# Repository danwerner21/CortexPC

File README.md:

# CortexPC

This is an ATX format implimentation of the Mini-Cortex system by Paul Ruizendaal and Stuart Conner.  The Mini-Cortex system is a further development of a TMS 9995 breadboard project to produce a system similar to a Powertran Cortex, but using more modern components. The system is based around a TMS 9995 running at 3 MHz, with 32K byte EEPROM, and will use 512K bytes of RAM  accessed through a memory mapper. An on-board serial port and IDE interface exists on the card.  There is also provisions for a TMS9918 clone, a keyboard and some expansion slots -- these are not totally supported by the firmware at this time however.

The main EEPROM image provides a boot menu which enables the user to select between the EVMBUG system monitor from TI's TMS 9995 Evaluation Module, a port of the Powertran Cortex Power BASIC made for a TM 990 computer, the Marinchip Disk Executive (MDEX) operating system, and an implementation of V6 Unix including a C compiler.

[Much more information can be found at Stuart's site](https://www.stuartconner.me.uk/mini_cortex/mini_cortex.htm)

[Source code for the Cortex Version of Unix V6 and a ton more TI990 software (including cross development tools) can be found here on Dave Pitts' TI-990 web page.](https://www.cozx.com/dpitts/ti990.html)

## Memory Map
The memory map is shown in the table below.

```
Memory Address	Mapped To
>0000 - >7FFF	ROM when enabled, otherwise RAM
>8000 - >EFFF	RAM
>F000 - >F0FB	TMS 9995 internal RAM
>F0FC - >FDFF	RAM
>FE00 - >FE03	CF card ATA registers 
>FE08 - >FE08	SN76489 SOUND
>FE20 - >FE21	Video
>FE40 - >FE4F	Memory mapper registers 0-15 
>FE60 - >FE7F	SID Chip
>FE80 - >FEBF	Offboard IO (ports $80-$FF)
>FFF0 - >FFF9	RAM
>FFFA - >FFFF	TMS 9995 internal RAM

CRU Address	Mapped To
>0000 - >003F	TMS 9902 registers
>0040 - >007F	Control signal latch (further details here)
 	(Plus processor internal CRU bits)
    
(Note that in TI Speak ">" means Hexidecimal, so for the rest of us >FFFA is the same as $FFFA or 0xFFFA or FFFAH)
```
[for more information see Stuart's site](https://www.stuartconner.me.uk/mini_cortex/mini_cortex.htm)

## Creating CF card Image for MDEX and Unix

The CF card has to be newly formatted with an MBR (master boot record), a single partition formatted as FAT32, and a cluster size of 4096 bytes - the CF card needs to be at least 256 MB to support this. Not all brands/sizes of CF card seem to work - you may have more success with an older, low capacity card. A SanDisk 2.0GB card with a "SDCFB" marking on the back works well.

It can be problematic formatting a new card using Windows 10 as it does not always seem to write an MBR to the card. I use a formatting utility called Rufus [details and download here](https://rufus.ie/en/) with Boot selection==Non bootable, Partition Scheme==MBR, File System=FAT32, and Cluster Size= 4096 Bytes. Once the card is correctly formatted, use Windows to write the four files from the software folder ZIP filedirectly to the card.
[for more information see Stuart's site](https://www.stuartconner.me.uk/mini_cortex/mini_cortex.htm)

## Jumper Settings
```
  P6 - ATX Case Power Button
  JP1- ATX Case Reset Button
  JP3- SID Chip CS (Some SID replacement chips need 2-3, default 1-2)
  J21- Enable SID Audio Amp
  J20- SID Speaker Out
  J22- SN76489 Audio Amp
  J23- SN76489 Speaker Out
  J1 - F18A TANG NANO Connector 
  J4 - Serial Interrupt Enabled (Required for UNIX)
  J5 - TTL Serial Interface
  J6 - TTL Serial Power Enable
  JP2- Enable Keyboard Interface
  JP4- ATX Case IDE Led output
  JP5- IDE Power Enable (2-3 for VCC on IDE Pin 20)
  
```
## Powering up
The serial port on the TMS9995 board is configured for 9600 Baud, 7 data bits, even parity, one stop bit, no flow control.

The EVMBUG monitor and the boot loaders for MDEX and Unix, are stored on a single 32K byte EEPROM. The required application is selected from a boot menu. To display the boot menu, connect the board to a configured serial port on a PC, apply power then press any key.

You should then see:
```
  ___         _           ___  ___
 / __|___ _ _| |_ _____ _| _ \/ __|
| (__/ _ \ '_|  _/ -_) \ /  _/ (__
 \___\___/_|  \__\___/_\_\_|  \___|

TMS9995 COMPUTER SYSTEM
BIOS V1.0

PRESS 1 FOR EVMBUG MONITOR
PRESS 2 FOR MDEX
PRESS 3 FOR UNIX
```
To select a software application from the menu, press the corresponding numeric key.

## Useful Links
MDEX documentation is available on the site http://www.powertrancortex.com/documentation.html. The documentation and MDEX disks were recovered and made available by Dave Hunter, the owner of the www.powertrancortex.com site. Porting of the MDEX files to the Mini-Cortex was by Paul Ruizendaal. On the Mini-Cortex, the files are stored in two emulated disks on the CF card.

The first version of Unix ported was LSX Unix (https://www.mailcom.com/lsx/), which was designed to run with 40K byte RAM and two 256K byte floppies. LSX Unix was adapted from Unix V6 by Dr. Heinz Lycklama (https://www.60bits.net/msu/mycomp/terak/termubel.htm). This port has been further ported to the TI 990 minicomputer by Dave Pitts, who has also made improvements to the code build system.

[Dave Pitts' TI-990 web page.](https://www.cozx.com/dpitts/ti990.html)
[EVMBUG documentation](https://www.stuartconner.me.uk/tibug_evmbug/tibug_evmbug.htm#evmbug)

## Bugs/To Do
* No known bugs in V0.9
* Keyboard Firmware needs created and tested

## Troubleshooting

The first test image tests just the processor (TMS9995_test_1_eprom_image), the EPROM and the EPROM chip select logic. Program and fit the EPROM, power on, press the reset switch.  The CPU should execute a loop from ROM., then use the logic probe to check for a series of pulses on pin 20 of the EPROM every 2 seconds or so. 

If the first test passes, repeat with the second test image (TMS9995_test_2_eprom_image), which also tests the RAM and the RAM chip select logic. With the second test, a series of pulses should be seen on pin 20 of the EPROM every 6 seconds or so.

The third test image has two versions.   The first version configures the serial port to 9600 Baud, 7 bits/character, even parity, 2 stops bits, no flow control, and then loops continually sending the ASCII characters >21 ("!") to >7E .  This version tests most of the system including ROM and RAM.   The second version is a ROM only version. It also configures the serial port to 9600 Baud, 7 bits/character, even parity, 2 stops bits, no flow control, and then loops continually sending the ASCII characters >21 ("!") to >7E , but does not use any external RAM.

## Patches
* none needed for V0.9
 
## BOM
Reference|Value|Qty|Description
---------|-----|---|-----------
C1,C2,C3,C4,C5,C6,C7,C8,C9,C10,C11,C12,C13,C14,C15,C16,C17,C19,C21,C23,C25,C27,C29|0.1u|23|
C18,C20,C22,C24|10u|4|
C26|22u|1|
C28|47uF|1|
C30|1uF|1|Polarized capacitor
C31|10uF|1|Polarized capacitor
C32|0.1 uF|1|Unpolarized capacitor
C33|0.01 uF|1|Unpolarized capacitor
C34|100µF|1|
C35|0.1µF|1|
C40,C41|15pf|2|
D1|PWR|1|LED
D2|IDLE|1|LED
D3|MAP|1|LED
D5|1N5817|1|20V 1A Schottky Barrier Rectifier Diode, DO-41
D6|IDE ACT|1|LED
D8|Tx|1|LED
D9|Rx|1|LED
D10,D11|1N4148|2|100V 0.15A standard switching diode, DO-35
J1|F18A TANG NANO Connector|1|Generic connector, double row, 02x10, odd/even pin numbering scheme (row 1 odd numbers, row 2 even numbers), script generated (kicad-library-utils/schlib/autogen/connector/)
J2,J8,J11,J13,J15,J17|IRQ Selection|6|Generic connector, double row, 02x06, odd/even pin numbering scheme (row 1 odd numbers, row 2 even numbers), script generated (kicad-library-utils/schlib/autogen/connector/)
J3,J10,J12,J14,J16,J18|Bus_I_not_SA_8bit|6|8-bit ISA-PC bus connector
J4|Enable Serial Int|1|Generic connector, single row, 01x02, script generated
J5|TTL SERIAL 0|1|
J6|TTL SER 0 PWR|1|
J7|USER OUT|1|Generic connector, single row, 01x07, script generated
J9|AUDIO OUT|1|coaxial connector (BNC, SMA, SMB, SMC, Cinch/RCA, LEMO, ...)
J19|Parallel Keyboard IN|1|Generic connector, single row, 01x11, script generated
JP1|JUMPER|1|Generic connector, single row, 01x02, script generated (kicad-library-utils/schlib/autogen/connector/)
JP4|EXT IDE LED|1|
JP5|IDE PWR|1|
P1|14.31818 MHz CLK|1|
P4|8 BIT IDE (CF)|1|
P5|CONN_10X2|1|Generic connector, double row, 02x10, odd/even pin numbering scheme (row 1 odd numbers, row 2 even numbers), script generated (kicad-library-utils/schlib/autogen/connector/)
P6|POWER_SW|1|Generic connector, single row, 01x02, script generated (kicad-library-utils/schlib/autogen/connector/)
R1,R3,R6,R7,R11,R12,R13,R17|470|8|-- mixed values --
R2,R4,R8,R10,R14|10K|5|
R5|1000|1|Resistor
R9|10Ω|1|
R16,R18|10k|2|Resistor
SW1|RESET|1|Push button switch, generic, two pins
SW2|POWER|1|Push button switch, generic, two pins
U1|74LS14|1|
U2|74LS07|1|
U3|TMS9995-DIP_1|1|
U4|74LS04|1|
U5,U27|74LS74|2|-- mixed values --
U6|74LS112|1|
U7|SN76489|1|
U8|DS1233|1|
U9|SRAM_512K|1|512K x 8 Low Power CMOS RAM, DIP-32
U10|TMS9918 EMU|1|
U11,U30|GAL22V10|2|
U12,U13|74LS32|2|Quad 2-input OR
U14,U28,U29,U31|74LS244|4|Octal Buffer and Line Driver With 3-State Output, active-low enables, non-inverting outputs
U15|74LS138|1|
U17|74LS688|1|
U18|27C256|1|
U21|TMS9902A|1|
U22|74LS259|1|
U23|74LS612-DIP|1|
U25|74LS245|1|Octal BUS Transceivers, 3-State outputs
U26|74HCT14|1|Hex inverter schmitt trigger
Y1|12MHz|1|

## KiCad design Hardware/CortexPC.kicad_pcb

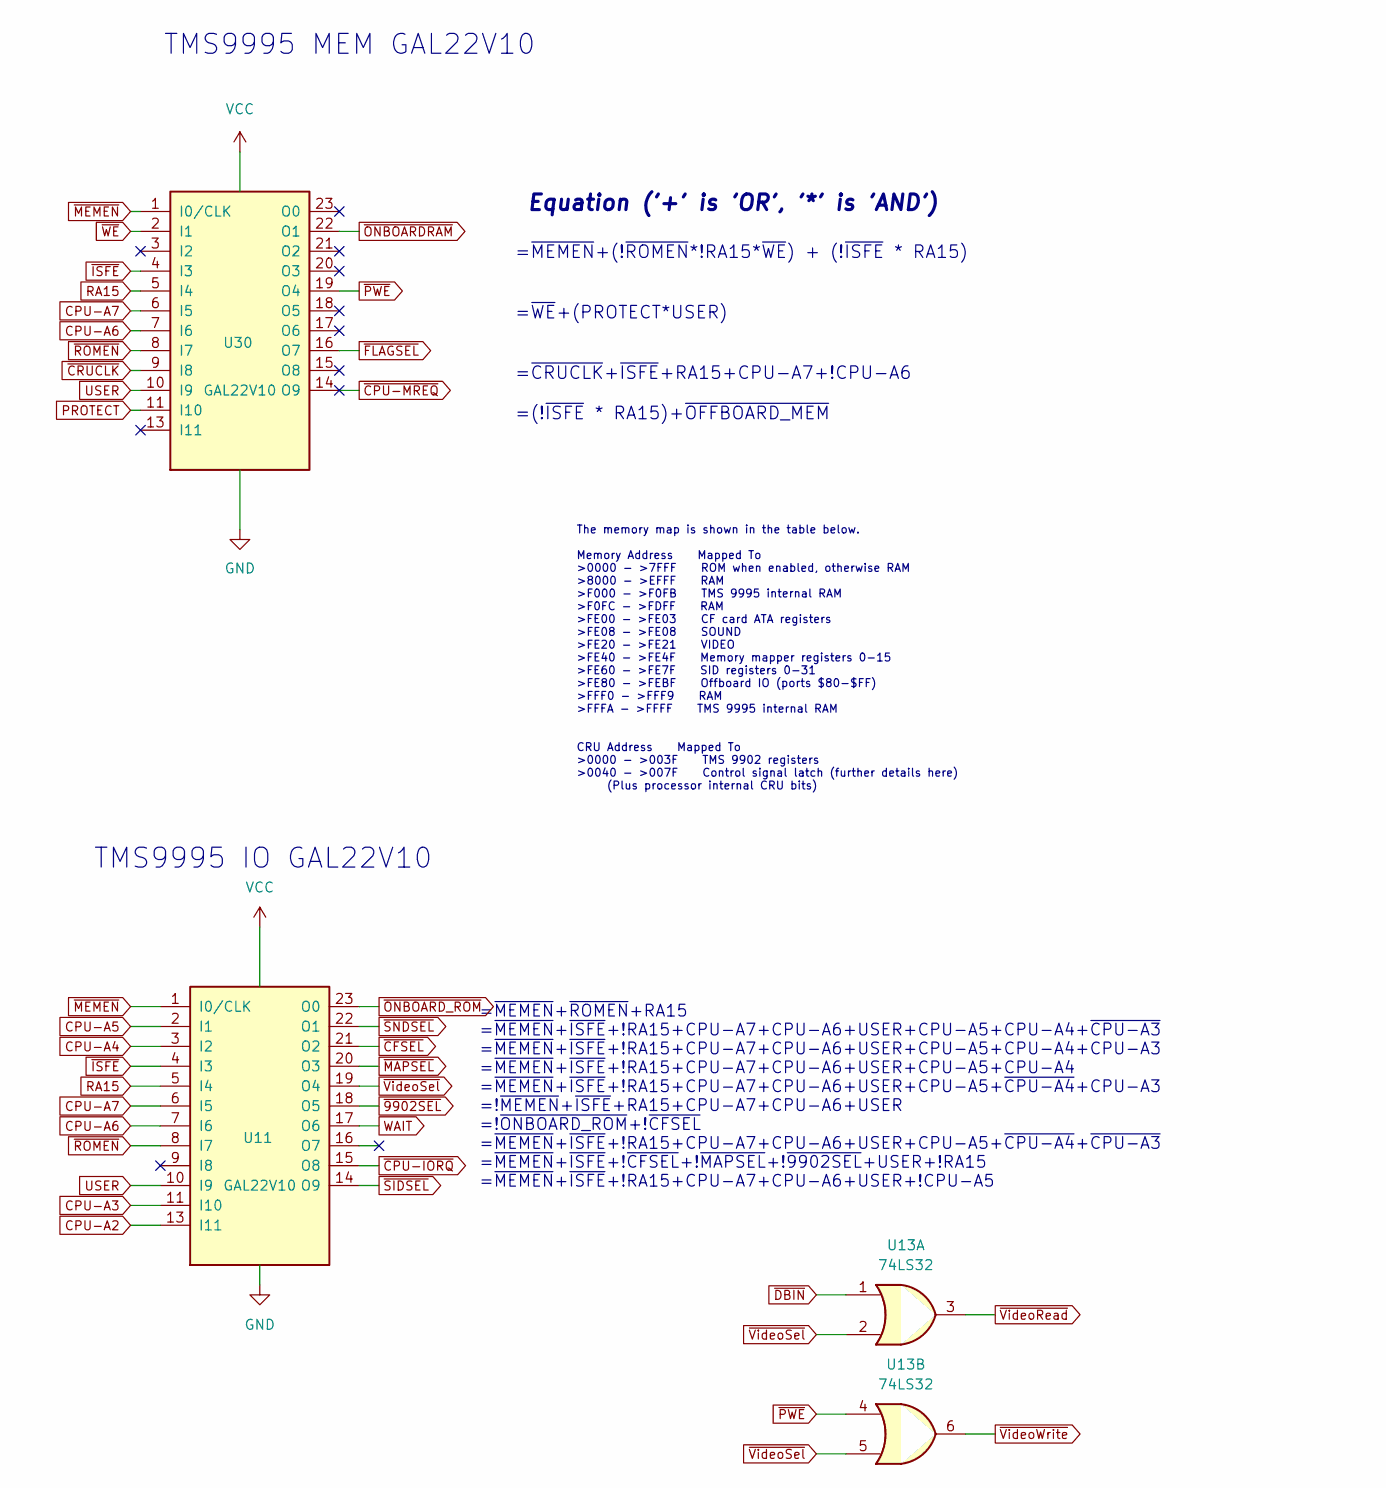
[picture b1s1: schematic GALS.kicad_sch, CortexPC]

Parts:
U11, U30: GAL22V10; STD_DDW_DIP24_Skinny
U13: 74LS32; STD_DDW_DIP14

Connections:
CPU-A2: U11.13 (I11); also elsewhere on the board
CPU-A3: U11.11 (I10); also elsewhere on the board
CPU-A4: U11.3 (I2); also elsewhere on the board
CPU-A5: U11.2 (I1); also elsewhere on the board
CPU-A6: U11.7 (I6), U30.7 (I6); also elsewhere on the board
CPU-A7: U11.6 (I5), U30.6 (I5); also elsewhere on the board
GND: U11.12 (GND), U30.12 (GND); also elsewhere on the board
PROTECT: U30.11 (I10); also elsewhere on the board
RA15: U11.5 (I4), U30.5 (I4); also elsewhere on the board
USER: U11.10 (I9), U30.10 (I9); also elsewhere on the board
VCC: U11.24 (VCC), U30.24 (VCC); also elsewhere on the board
WAIT: U11.17 (O6); also elsewhere on the board
~9902SEL: U11.18 (O5); also elsewhere on the board
~CFSEL: U11.21 (O2); also elsewhere on the board
~CPU-IORQ: U11.15 (O8); also elsewhere on the board
~CPU-MREQ: U30.14 (O9)
~CRUCLK: U30.9 (I8); also elsewhere on the board
~DBIN: U13.1; also elsewhere on the board
~FLAGSEL: U30.16 (O7); also elsewhere on the board
~ISFE: U11.4 (I3), U30.4 (I3); also elsewhere on the board
~MAPSEL: U11.20 (O3); also elsewhere on the board
~MEMEN: U11.1 (I0/CLK), U30.1 (I0/CLK); also elsewhere on the board
~ONBOARDRAM: U30.22 (O1); also elsewhere on the board
~ONBOARD_ROM: U11.23 (O0); also elsewhere on the board
~PWE: U13.4, U30.19 (O4); also elsewhere on the board
~ROMEN: U11.8 (I7), U30.8 (I7); also elsewhere on the board
~SIDSEL: U11.14 (O9); also elsewhere on the board
~SNDSEL: U11.22 (O1); also elsewhere on the board
~VideoRead: U13.3; also elsewhere on the board
~VideoSel: U11.19 (O4), U13.2, U13.5
~VideoWrite: U13.6; also elsewhere on the board
~WE: U30.2 (I1); also elsewhere on the board

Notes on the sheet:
=~{MEMEN}+(!~{ROMEN}*!RA15*~{WE}) + (!~{ISFE} * RA15) =~{WE}+(PROTECT*USER) =~{CRUCLK}+~{ISFE}+RA15+CPU-A7+!CPU-A6 =(!~{ISFE} * RA15)+~{OFFBOARD_MEM}
Equation ('+' is 'OR', '*' is 'AND')
TMS9995 MEM GAL22V10
The memory map is shown in the table below. Memory Address Mapped To >0000 - >7FFF ROM when enabled, otherwise RAM >8000 - >EFFF RAM >F000 - >F0FB TMS 9995 internal RAM >F0FC - >FDFF RAM >FE00 - >FE03 CF card ATA registers >FE08 - >FE08 SOUND >FE20 - >FE21 VIDEO >FE40 - >FE4F Memory mapper register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
TMS9995 IO GAL22V10
=~{MEMEN}+~{ROMEN}+RA15 =~{MEMEN}+~{ISFE}+!RA15+CPU-A7+CPU-A6+USER+CPU-A5+CPU-A4+~{CPU-A3} =~{MEMEN}+~{ISFE}+!RA15+CPU-A7+CPU-A6+USER+CPU-A5+CPU-A4+CPU-A3 =~{MEMEN}+~{ISFE}+!RA15+CPU-A7+CPU-A6+USER+CPU-A5+CPU-A4 =~{MEMEN}+~{ISFE}+!RA15+CPU-A7+CPU-A6+USER+CPU-A5+~{CPU-A4}+CPU-A3 =!~{MEMEN}+~{ISFE}+R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

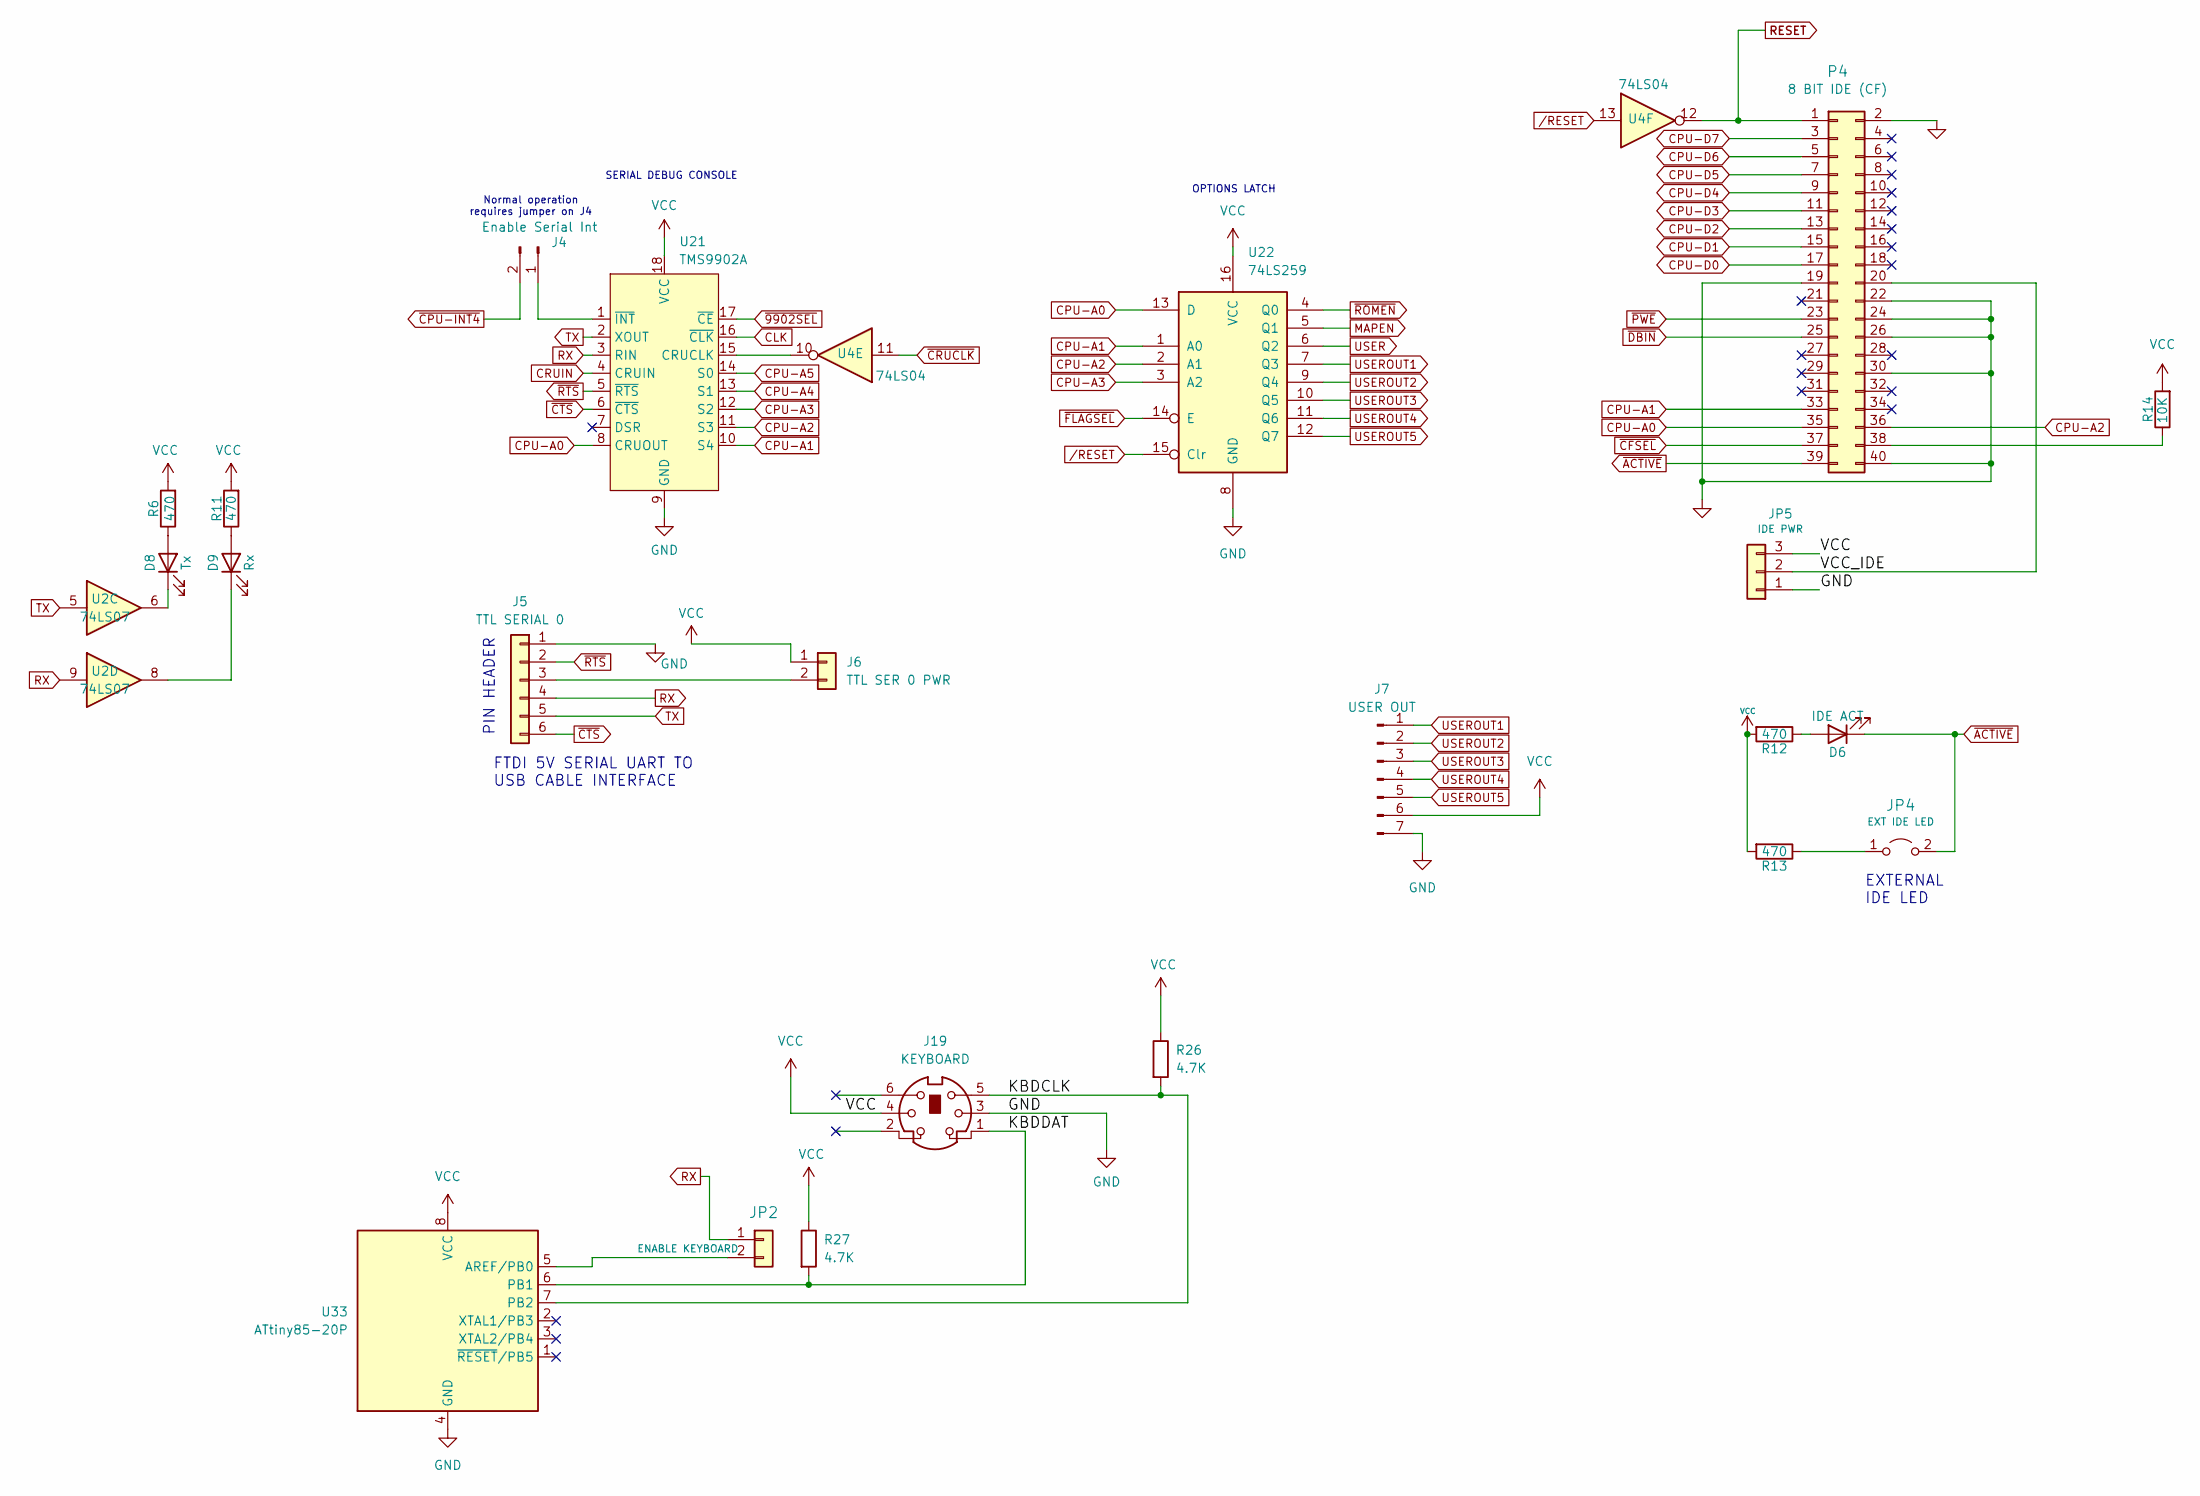
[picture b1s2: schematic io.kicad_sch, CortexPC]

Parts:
D6: IDE ACT; STD_DDW_LED5
D8: Tx; STD_DDW_LED5
D9: Rx; STD_DDW_LED5
J4: Enable Serial Int; STD_DDW_PINHEAD_V_1x02
J5: TTL SERIAL 0; STD_DDW_PINHEAD_V_1x06
J6: TTL SER 0 PWR; STD_DDW_PINHEAD_V_1x02
J7: USER OUT; STD_DDW_PINHEAD_V_1x07
J19: KEYBOARD; PS2_DIN
JP2: ENABLE KEYBOARD; STD_DDW_PINHEAD_V_1x02
JP4: EXT IDE LED; STD_DDW_PINHEAD_V_1x02
JP5: IDE PWR; STD_DDW_PINHEAD_V_1x03
P4: 8 BIT IDE (CF); STD_DDW_PINHEAD_V_2x20
R6, R11, R12, R13: 470; STD_DDW_RESISTOR
R14: 10K; STD_DDW_RESISTOR
R26, R27: 4.7K; STD_DDW_RESISTOR
U2: 74LS07; STD_DDW_DIP14
U4: 74LS04; STD_DDW_DIP14
U21: TMS9902A; STD_DDW_DIP18
U22: 74LS259; STD_DDW_DIP16
U33: ATtiny85-20P; STD_DDW_DIP8

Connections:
/IO/KBDCLK: J19.5, R26.2, U33.7 (PB2)
/IO/KBDDAT: J19.1, R27.2, U33.6 (PB1)
/IO/VCC_IDE: JP5.2, P4.20
CLK: U21.16 (~CLK); also elsewhere on the board
CPU-A0: P4.35, U21.8 (CRUOUT), U22.13 (D); also elsewhere on the board
CPU-A1: P4.33, U21.10 (S4), U22.1 (A0); also elsewhere on the board
CPU-A2: P4.36, U21.11 (S3), U22.2 (A1); also elsewhere on the board
CPU-A3: U21.12 (S2), U22.3 (A2); also elsewhere on the board
CPU-A4: U21.13 (S1); also elsewhere on the board
CPU-A5: U21.14 (S0); also elsewhere on the board
CPU-D0: P4.17; also elsewhere on the board
CPU-D1: P4.15; also elsewhere on the board
CPU-D2: P4.13; also elsewhere on the board
CPU-D3: P4.11; also elsewhere on the board
CPU-D4: P4.9; also elsewhere on the board
CPU-D5: P4.7; also elsewhere on the board
CPU-D6: P4.5; also elsewhere on the board
CPU-D7: P4.3; also elsewhere on the board
CRUIN: U21.4 (CRUIN); also elsewhere on the board
GND: J5.1, J7.7, J19.3, JP5.1, P4.2, P4.19, P4.22, P4.24, P4.26, P4.30, P4.40, U21.9 (GND), U22.8 (GND), U33.4 (GND); also elsewhere on the board
MAPEN: U22.5 (Q1); also elsewhere on the board
unnamed: D6.2 (A), R12.1
unnamed: D8.2 (A), R6.1
unnamed: D8.1 (K), U2.6
unnamed: D9.2 (A), R11.1
unnamed: D9.1 (K), U2.8
unnamed: J4.1, U21.1 (~INT)
unnamed: J5.3, J6.2
unnamed: JP2.2, U33.5 (AREF/PB0)
unnamed: JP4.1 (A), R13.1
unnamed: P4.38, R14.1
unnamed: U4.10, U21.15 (CRUCLK)
RESET: P4.1, U4.12; also elsewhere on the board
RX: J5.4, JP2.1, U2.9, U21.3 (RIN)
TX: J5.5, U2.5, U21.2 (XOUT)
USER: U22.6 (Q2); also elsewhere on the board
USEROUT1: J7.1, U22.7 (Q3)
USEROUT2: J7.2, U22.9 (Q4)
USEROUT3: J7.3, U22.10 (Q5)
USEROUT4: J7.4, U22.11 (Q6)
USEROUT5: J7.5, U22.12 (Q7)
VCC: J6.1, J7.6, J19.4, JP5.3, R6.2, R11.2, R12.2, R13.2, R14.2, R26.1, R27.1, U21.18 (VCC), U22.16 (VCC), U33.8 (VCC); also elsewhere on the board
/RESET: U4.13, U22.15 (Clr); also elsewhere on the board
~9902SEL: U21.17 (~CE); also elsewhere on the board
~ACTIVE: D6.1 (K), JP4.2 (B), P4.39
~CFSEL: P4.37; also elsewhere on the board
~CPU-INT4: J4.2; also elsewhere on the board
~CRUCLK: U4.11; also elsewhere on the board
~CTS: J5.6, U21.6 (~CTS)
~DBIN: P4.25; also elsewhere on the board
~FLAGSEL: U22.14 (E); also elsewhere on the board
~PWE: P4.23; also elsewhere on the board
~ROMEN: U22.4 (Q0); also elsewhere on the board
~RTS: J5.2, U21.5 (~RTS)

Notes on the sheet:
Normal operation requires jumper on J4
PIN HEADER
FTDI 5V SERIAL UART TO USB CABLE INTERFACE
EXTERNAL IDE LED
SERIAL DEBUG CONSOLE
OPTIONS LATCH

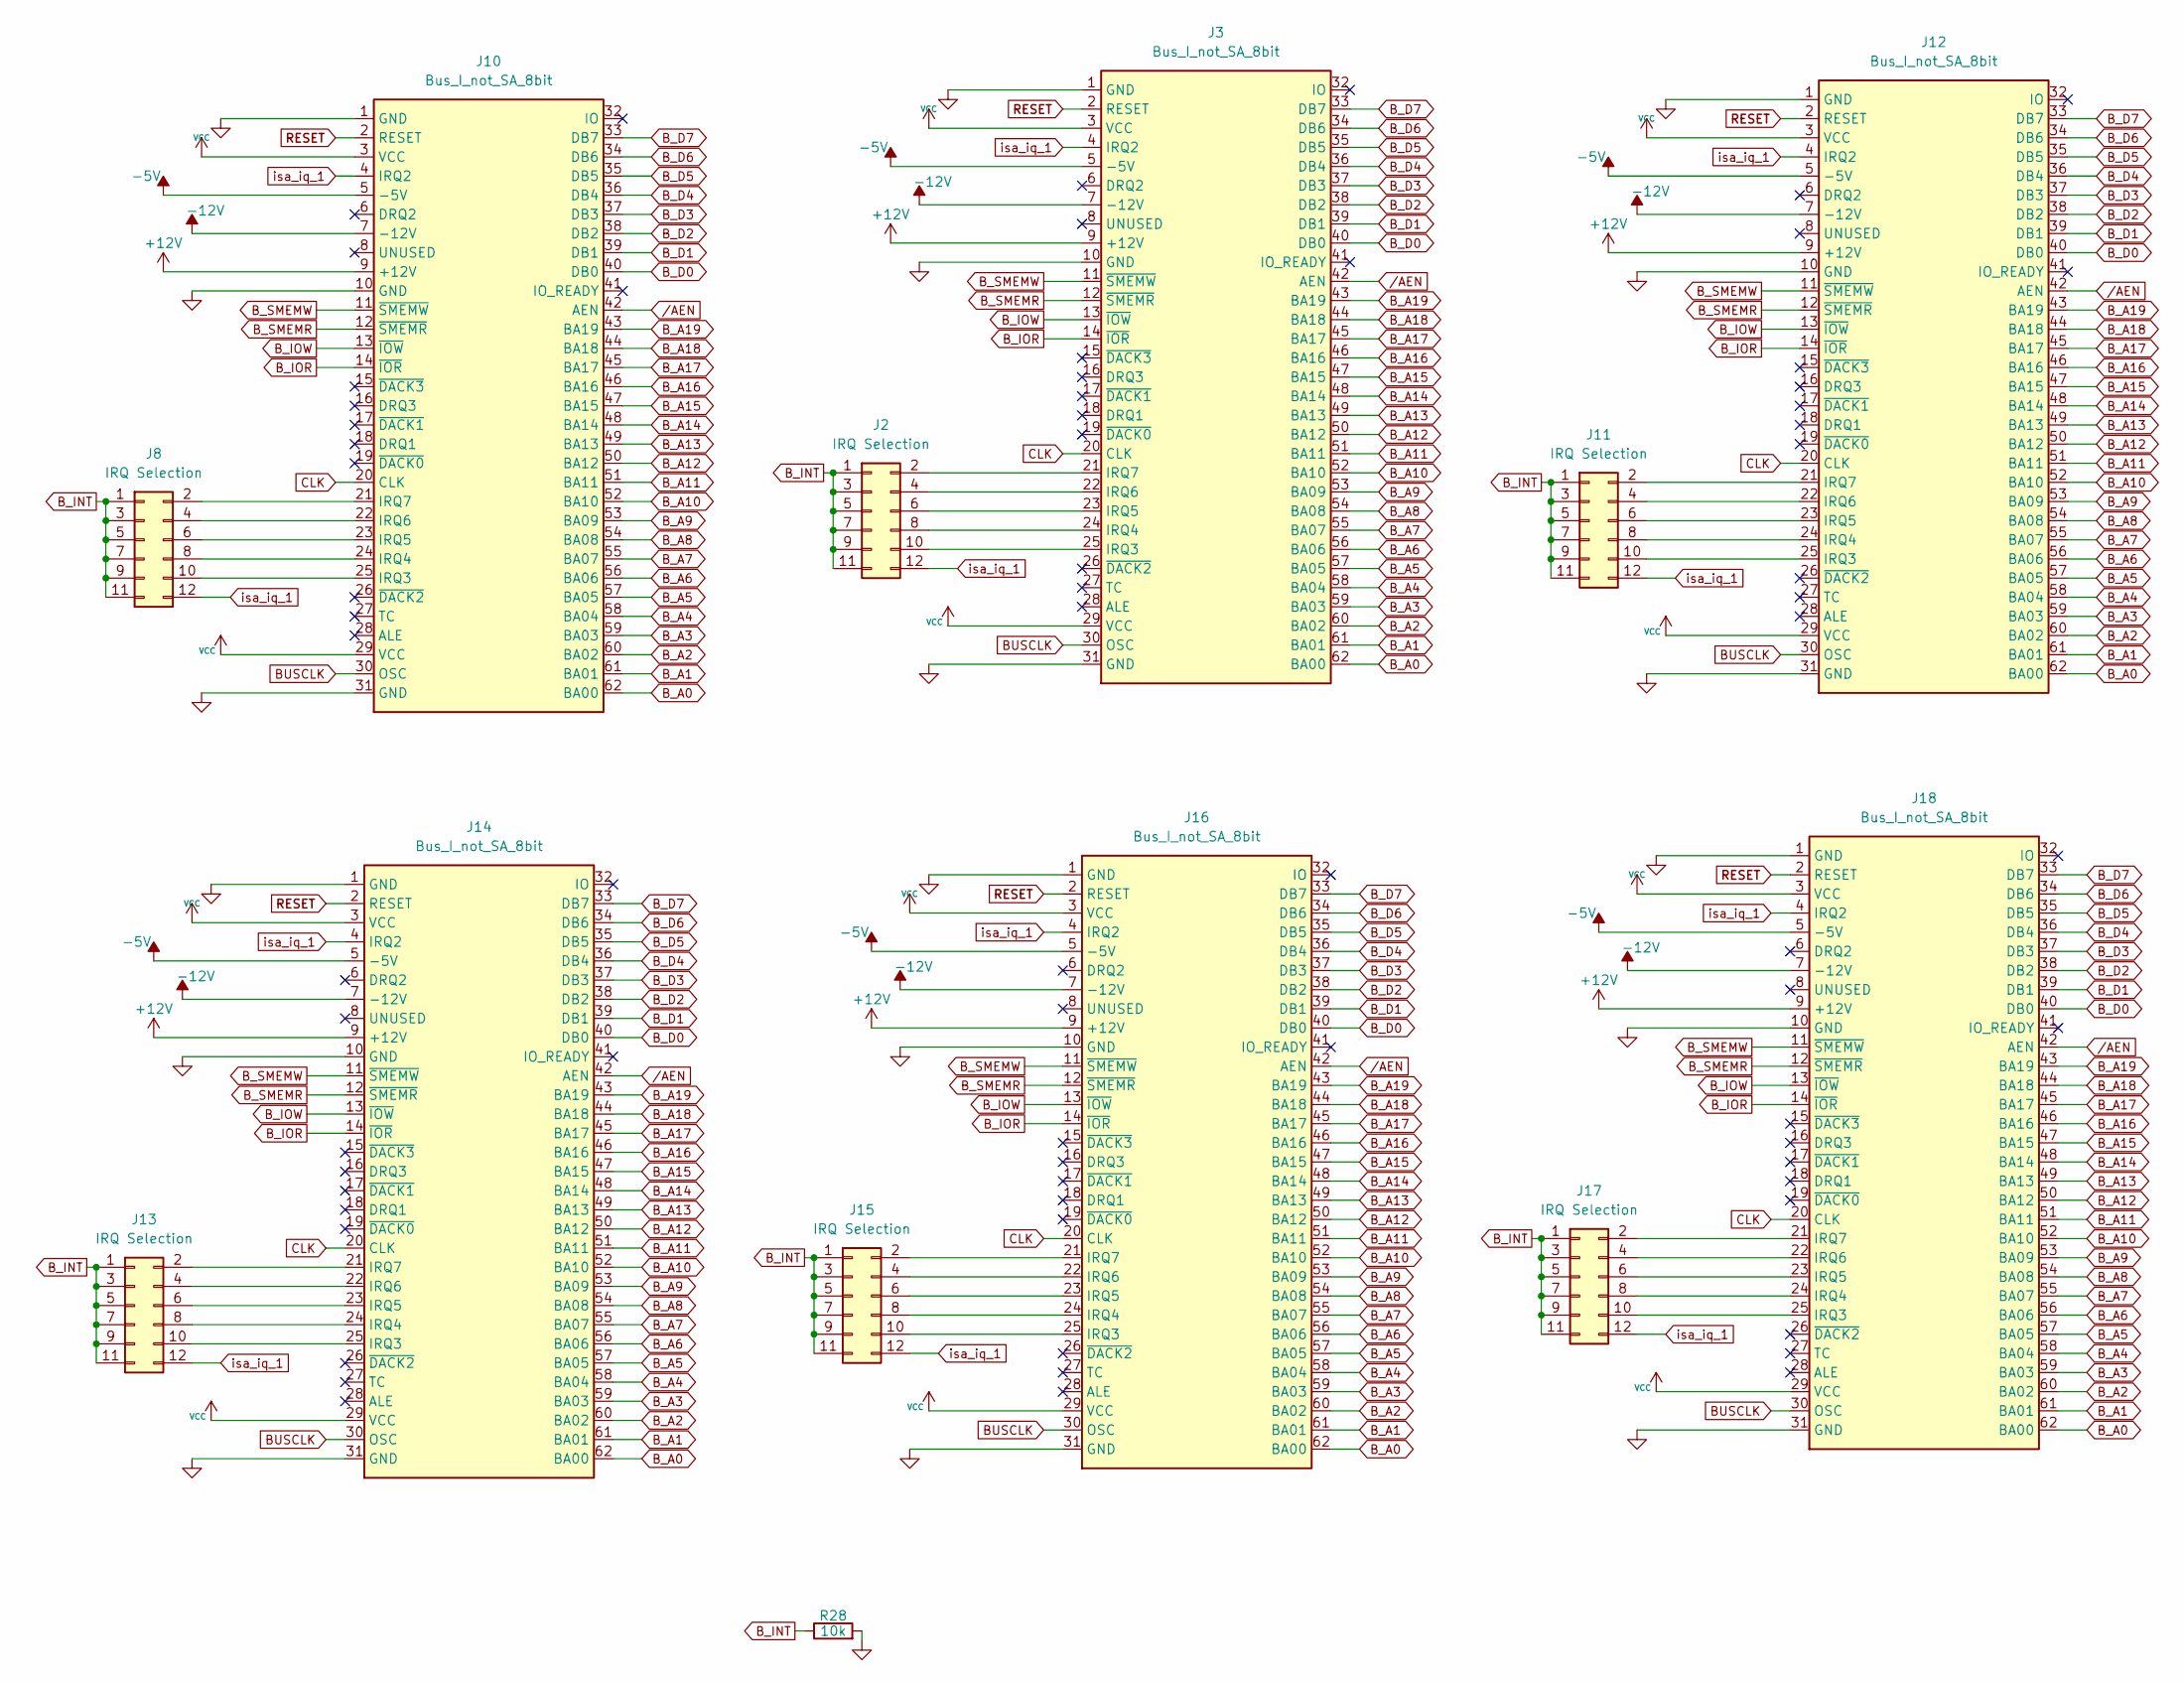
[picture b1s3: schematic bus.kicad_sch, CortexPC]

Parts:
J2, J8, J11, J13, J15, J17: IRQ Selection; STD_DDW_PINHEAD_V_2x06
J3, J10, J12, J14, J16, J18: Bus_I_not_SA_8bit; BUSPC_HOST
R28: 10k; STD_DDW_RESISTOR

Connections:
+12V: J3.9 (+12V), J10.9 (+12V), J12.9 (+12V), J14.9 (+12V), J16.9 (+12V), J18.9 (+12V); also elsewhere on the board
-5V: J3.5 (-5V), J10.5 (-5V), J12.5 (-5V), J14.5 (-5V), J16.5 (-5V), J18.5 (-5V); also elsewhere on the board
-12V: J3.7 (-12V), J10.7 (-12V), J12.7 (-12V), J14.7 (-12V), J16.7 (-12V), J18.7 (-12V); also elsewhere on the board
BUSCLK: J3.30 (OSC), J10.30 (OSC), J12.30 (OSC), J14.30 (OSC), J16.30 (OSC), J18.30 (OSC); also elsewhere on the board
B_A0: J3.62 (BA00), J10.62 (BA00), J12.62 (BA00), J14.62 (BA00), J16.62 (BA00), J18.62 (BA00); also elsewhere on the board
B_A1: J3.61 (BA01), J10.61 (BA01), J12.61 (BA01), J14.61 (BA01), J16.61 (BA01), J18.61 (BA01); also elsewhere on the board
B_A2: J3.60 (BA02), J10.60 (BA02), J12.60 (BA02), J14.60 (BA02), J16.60 (BA02), J18.60 (BA02); also elsewhere on the board
B_A3: J3.59 (BA03), J10.59 (BA03), J12.59 (BA03), J14.59 (BA03), J16.59 (BA03), J18.59 (BA03); also elsewhere on the board
B_A4: J3.58 (BA04), J10.58 (BA04), J12.58 (BA04), J14.58 (BA04), J16.58 (BA04), J18.58 (BA04); also elsewhere on the board
B_A5: J3.57 (BA05), J10.57 (BA05), J12.57 (BA05), J14.57 (BA05), J16.57 (BA05), J18.57 (BA05); also elsewhere on the board
B_A6: J3.56 (BA06), J10.56 (BA06), J12.56 (BA06), J14.56 (BA06), J16.56 (BA06), J18.56 (BA06); also elsewhere on the board
B_A7: J3.55 (BA07), J10.55 (BA07), J12.55 (BA07), J14.55 (BA07), J16.55 (BA07), J18.55 (BA07); also elsewhere on the board
B_A8: J3.54 (BA08), J10.54 (BA08), J12.54 (BA08), J14.54 (BA08), J16.54 (BA08), J18.54 (BA08); also elsewhere on the board
B_A9: J3.53 (BA09), J10.53 (BA09), J12.53 (BA09), J14.53 (BA09), J16.53 (BA09), J18.53 (BA09); also elsewhere on the board
B_A10: J3.52 (BA10), J10.52 (BA10), J12.52 (BA10), J14.52 (BA10), J16.52 (BA10), J18.52 (BA10); also elsewhere on the board
B_A11: J3.51 (BA11), J10.51 (BA11), J12.51 (BA11), J14.51 (BA11), J16.51 (BA11), J18.51 (BA11); also elsewhere on the board
B_A12: J3.50 (BA12), J10.50 (BA12), J12.50 (BA12), J14.50 (BA12), J16.50 (BA12), J18.50 (BA12); also elsewhere on the board
B_A13: J3.49 (BA13), J10.49 (BA13), J12.49 (BA13), J14.49 (BA13), J16.49 (BA13), J18.49 (BA13); also elsewhere on the board
B_A14: J3.48 (BA14), J10.48 (BA14), J12.48 (BA14), J14.48 (BA14), J16.48 (BA14), J18.48 (BA14); also elsewhere on the board
B_A15: J3.47 (BA15), J10.47 (BA15), J12.47 (BA15), J14.47 (BA15), J16.47 (BA15), J18.47 (BA15); also elsewhere on the board
B_A16: J3.46 (BA16), J10.46 (BA16), J12.46 (BA16), J14.46 (BA16), J16.46 (BA16), J18.46 (BA16); also elsewhere on the board
B_A17: J3.45 (BA17), J10.45 (BA17), J12.45 (BA17), J14.45 (BA17), J16.45 (BA17), J18.45 (BA17); also elsewhere on the board
B_A18: J3.44 (BA18), J10.44 (BA18), J12.44 (BA18), J14.44 (BA18), J16.44 (BA18), J18.44 (BA18); also elsewhere on the board
B_A19: J3.43 (BA19), J10.43 (BA19), J12.43 (BA19), J14.43 (BA19), J16.43 (BA19), J18.43 (BA19); also elsewhere on the board
B_D0: J3.40 (DB0), J10.40 (DB0), J12.40 (DB0), J14.40 (DB0), J16.40 (DB0), J18.40 (DB0); also elsewhere on the board
B_D1: J3.39 (DB1), J10.39 (DB1), J12.39 (DB1), J14.39 (DB1), J16.39 (DB1), J18.39 (DB1); also elsewhere on the board
B_D2: J3.38 (DB2), J10.38 (DB2), J12.38 (DB2), J14.38 (DB2), J16.38 (DB2), J18.38 (DB2); also elsewhere on the board
B_D3: J3.37 (DB3), J10.37 (DB3), J12.37 (DB3), J14.37 (DB3), J16.37 (DB3), J18.37 (DB3); also elsewhere on the board
B_D4: J3.36 (DB4), J10.36 (DB4), J12.36 (DB4), J14.36 (DB4), J16.36 (DB4), J18.36 (DB4); also elsewhere on the board
B_D5: J3.35 (DB5), J10.35 (DB5), J12.35 (DB5), J14.35 (DB5), J16.35 (DB5), J18.35 (DB5); also elsewhere on the board
B_D6: J3.34 (DB6), J10.34 (DB6), J12.34 (DB6), J14.34 (DB6), J16.34 (DB6), J18.34 (DB6); also elsewhere on the board
B_D7: J3.33 (DB7), J10.33 (DB7), J12.33 (DB7), J14.33 (DB7), J16.33 (DB7), J18.33 (DB7); also elsewhere on the board
B_INT: J2.1, J2.3, J2.5, J2.7, J2.9, J2.11, J8.1, J8.3, J8.5, J8.7, J8.9, J8.11, J11.1, J11.3, J11.5, J11.7, J11.9, J11.11, J13.1, J13.3, J13.5, J13.7, J13.9, J13.11, J15.1, J15.3, J15.5, J15.7, J15.9, J15.11, J17.1, J17.3, J17.5, J17.7, J17.9, J17.11, R28.1; also elsewhere on the board
B_IOR: J3.14 (~IOR), J10.14 (~IOR), J12.14 (~IOR), J14.14 (~IOR), J16.14 (~IOR), J18.14 (~IOR); also elsewhere on the board
B_IOW: J3.13 (~IOW), J10.13 (~IOW), J12.13 (~IOW), J14.13 (~IOW), J16.13 (~IOW), J18.13 (~IOW); also elsewhere on the board
B_SMEMR: J3.12 (~SMEMR), J10.12 (~SMEMR), J12.12 (~SMEMR), J14.12 (~SMEMR), J16.12 (~SMEMR), J18.12 (~SMEMR); also elsewhere on the board
B_SMEMW: J3.11 (~SMEMW), J10.11 (~SMEMW), J12.11 (~SMEMW), J14.11 (~SMEMW), J16.11 (~SMEMW), J18.11 (~SMEMW); also elsewhere on the board
CLK: J3.20 (CLK), J10.20 (CLK), J12.20 (CLK), J14.20 (CLK), J16.20 (CLK), J18.20 (CLK); also elsewhere on the board
GND: J3.1 (GND), J3.10 (GND), J3.31 (GND), J10.1 (GND), J10.10 (GND), J10.31 (GND), J12.1 (GND), J12.10 (GND), J12.31 (GND), J14.1 (GND), J14.10 (GND), J14.31 (GND), J16.1 (GND), J16.10 (GND), J16.31 (GND), J18.1 (GND), J18.10 (GND), J18.31 (GND), R28.2; also elsewhere on the board
unnamed: J2.2, J3.21 (IRQ7)
unnamed: J2.4, J3.22 (IRQ6)
unnamed: J2.6, J3.23 (IRQ5)
unnamed: J2.8, J3.24 (IRQ4)
unnamed: J2.10, J3.25 (IRQ3)
unnamed: J8.10, J10.25 (IRQ3)
unnamed: J8.8, J10.24 (IRQ4)
unnamed: J8.6, J10.23 (IRQ5)
unnamed: J8.4, J10.22 (IRQ6)
unnamed: J8.2, J10.21 (IRQ7)
unnamed: J11.2, J12.21 (IRQ7)
unnamed: J11.4, J12.22 (IRQ6)
unnamed: J11.6, J12.23 (IRQ5)
unnamed: J11.8, J12.24 (IRQ4)
unnamed: J11.10, J12.25 (IRQ3)
unnamed: J13.2, J14.21 (IRQ7)
unnamed: J13.4, J14.22 (IRQ6)
unnamed: J13.6, J14.23 (IRQ5)
unnamed: J13.8, J14.24 (IRQ4)
unnamed: J13.10, J14.25 (IRQ3)
unnamed: J15.2, J16.21 (IRQ7)
unnamed: J15.4, J16.22 (IRQ6)
unnamed: J15.6, J16.23 (IRQ5)
unnamed: J15.8, J16.24 (IRQ4)
unnamed: J15.10, J16.25 (IRQ3)
unnamed: J17.2, J18.21 (IRQ7)
unnamed: J17.4, J18.22 (IRQ6)
unnamed: J17.6, J18.23 (IRQ5)
unnamed: J17.8, J18.24 (IRQ4)
unnamed: J17.10, J18.25 (IRQ3)
RESET: J3.2 (RESET), J10.2 (RESET), J12.2 (RESET), J14.2 (RESET), J16.2 (RESET), J18.2 (RESET); also elsewhere on the board
VCC: J3.3 (VCC), J3.29 (VCC), J10.3 (VCC), J10.29 (VCC), J12.3 (VCC), J12.29 (VCC), J14.3 (VCC), J14.29 (VCC), J16.3 (VCC), J16.29 (VCC), J18.3 (VCC), J18.29 (VCC); also elsewhere on the board
isa_iq_1: J2.12, J3.4 (IRQ2), J8.12, J10.4 (IRQ2), J11.12, J12.4 (IRQ2), J13.12, J14.4 (IRQ2), J15.12, J16.4 (IRQ2), J17.12, J18.4 (IRQ2)
/AEN: J3.42 (AEN), J10.42 (AEN), J12.42 (AEN), J14.42 (AEN), J16.42 (AEN), J18.42 (AEN); also elsewhere on the board
